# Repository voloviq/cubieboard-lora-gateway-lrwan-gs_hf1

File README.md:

# cubieboard-lora-gateway-lrwan-gs_hf1
Cubieboard 1 carrier board for Loragateway lrwan-gs_hf1

PCB View

This is first prototype version and can have some connection mistakes. Please check it before use!.

This update was made in lates KiCad version 5.99.

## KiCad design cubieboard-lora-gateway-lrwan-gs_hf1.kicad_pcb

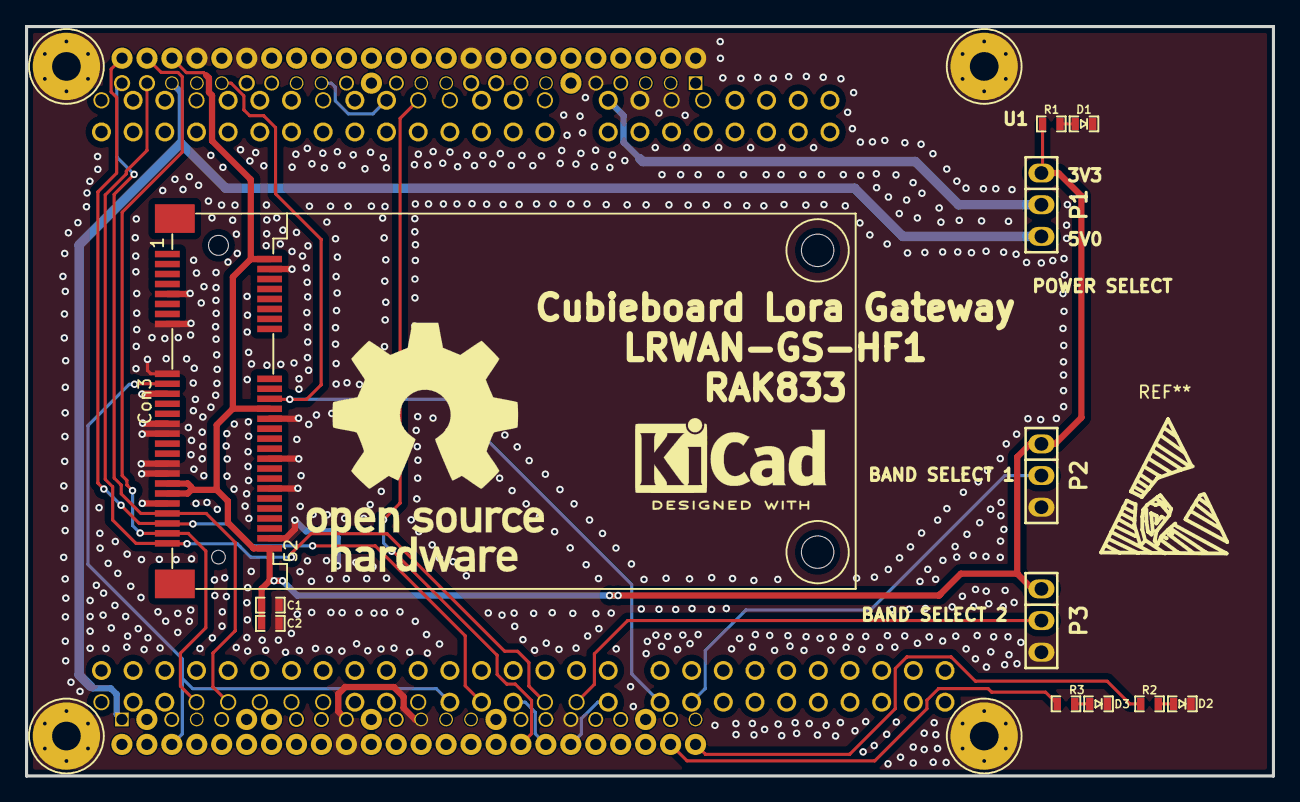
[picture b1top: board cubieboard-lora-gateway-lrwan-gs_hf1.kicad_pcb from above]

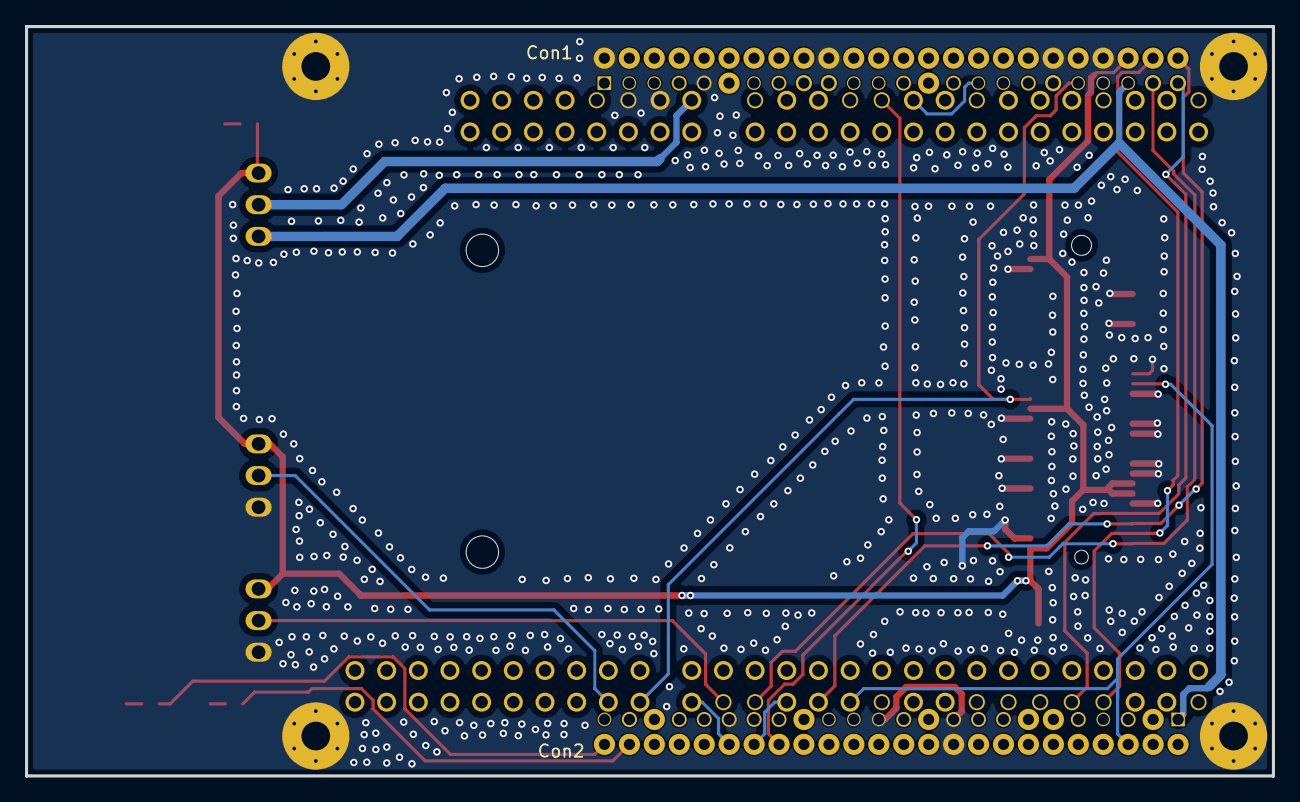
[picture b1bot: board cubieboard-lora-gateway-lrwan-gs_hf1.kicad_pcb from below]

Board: 2 copper layers, 100.0 x 60.1 mm, 19 parts (2 on the bottom side), 21 nets.

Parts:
C1: 100n; 100nF_0603
C2: 10uF; 10uF_10V_0603
Con1, Con2: Header_Socket_2x26; Header_Socket_2x26pin
Con3: 2041119-1
D1: KPG-1608SURKC-T; LED_KPG-1608SURKC-T
D2, D3: KPT-1608CGCK; LED_KPT-1608CGCK
MH1, MH2, MH3, MH4: MW_M2_Grounded; Mounting_Hole_M2_Grounded
P1: Power_Sel; Goldpin_3_2_54mm
P2: Band_Sel1; Goldpin_3_2_54mm
P3: Band_Sel2; Goldpin_3_2_54mm
R1, R2, R3: 220R; 220R_0603
U1: LRWAN_GS_HF1

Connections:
3V3: C1.1, C2.1, Con1.44, Con3.2, Con3.24, Con3.39, Con3.41, Con3.52, P1.1, P2.1, P3.1, R1.1
5V: Con1.43, Con2.1, P1.3
/PB2_PWM0: Con1.31, U1.27 (GPIO3-PF10)
/PB11/I2S_D03: Con1.39, Con3.22, U1.66 (RST-PF12)
/PB18/TWI1_SCK: Con2.6, Con3.19, U1.78 (GPIO2-PF15)
/PE4/TS0_D0: Con2.34, U1.25 (GPIO4-PF5)
/PE5/TS0_D1/CSI0_D1/SMC_VPPEN: Con2.36, U1.74 (GPIO1-PF14)
/PE6/TS0_D2/CSI0_D2: Con2.38, U1.68 (GPIO0-PF13)
/PE10/TS0_D6/CSI0_D6: Con2.46, R3.1
/PE11/TS0_D7/CSI0_D7: Con2.48, R2.1
/PI10/SPI0_CS0/UART5_TX/EINT22: Con1.45, Con3.51, U1.72 (CSN-PE11)
/PI11/SPI0_CLK/UART5_RX: Con1.47, Con3.45, U1.92 (SCK-PE12)
/PI12/SPI0_MOSI/UART6_TX/EINT24: Con1.46, Con3.49, U1.94 (MOSI-PE14)
/PI13/SPI0_MISO/UART6_RX/EINT25: Con1.48, Con3.47, U1.76 (MISO-PE13)
GND: C1.2, C2.2, Con1.2, Con1.9, Con1.20, Con1.38, Con1.42, Con2.19, Con2.20, Con2.25, Con2.37, Con3.4, Con3.9, Con3.15, Con3.17, Con3.21, Con3.26, Con3.27, Con3.29, Con3.34, Con3.35, Con3.37, Con3.40, Con3.43, Con3.50, D1.2 (K), D2.2 (K), D3.2 (K), MH1.1, MH2.1, MH3.1, MH4.1, P2.3, P3.3, U1.11 (GND), U1.13 (GND)
unnamed: D1.1 (A), R1.2
unnamed: D2.1 (A), R2.2
unnamed: D3.1 (A), R3.2
unnamed: P1.2, U1.15 (VIN)
unnamed: P2.2, U1.64 (BAND_SET1_PD15)
unnamed: P3.2, U1.70 (BAND_SET2_PE9)

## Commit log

2021-05-25 Initial
2021-05-25 Finalized project
2021-06-09 Applied issue
